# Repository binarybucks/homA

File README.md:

# HomA   

HomA is a free and open source framework for building smart homes and connecting them to the internet of things. 
It is designed to provide an entry into the world of home automation while also remaining highly extensible and adaptable for advanced users. 

To facilitate the development of own hardware and software extensions, HomA relies on completely open technologies and standards that are available on many platforms. Hence, it uses the lightweight and open [MQTT protocol](http://mqtt.org/faq) for both data storage and command transmission. 

### Getting started
Getting started with HomA is quite easy and requries just some basic Linux and commandline knowledge. For detailed installation instructions, please refer to the [Installation page](https://github.com/binarybucks/homA/wiki/Installation) on the Wiki.

### Components 
A list of offical components is available in the [wiki](https://github.com/binarybucks/homA/wiki/Components). 

### Contribute
Fork the repository on GitHub, add your own improvements, push it to a branch in your fork and send us a pull request. An overview of open tasks is available on the [Waffle.io](http://waffle.io/binarybucks/homA) dashboard.
You can also file bugs or feature requests in our [issue tracker](https://github.com/binarybucks/homA/issues) or say hi in our [Google+ Community](https://plus.google.com/u/0/communities/111676474572375715081).

### License
If not stated otherwise explicitly, any code in this repository is licensed under the EPL license.

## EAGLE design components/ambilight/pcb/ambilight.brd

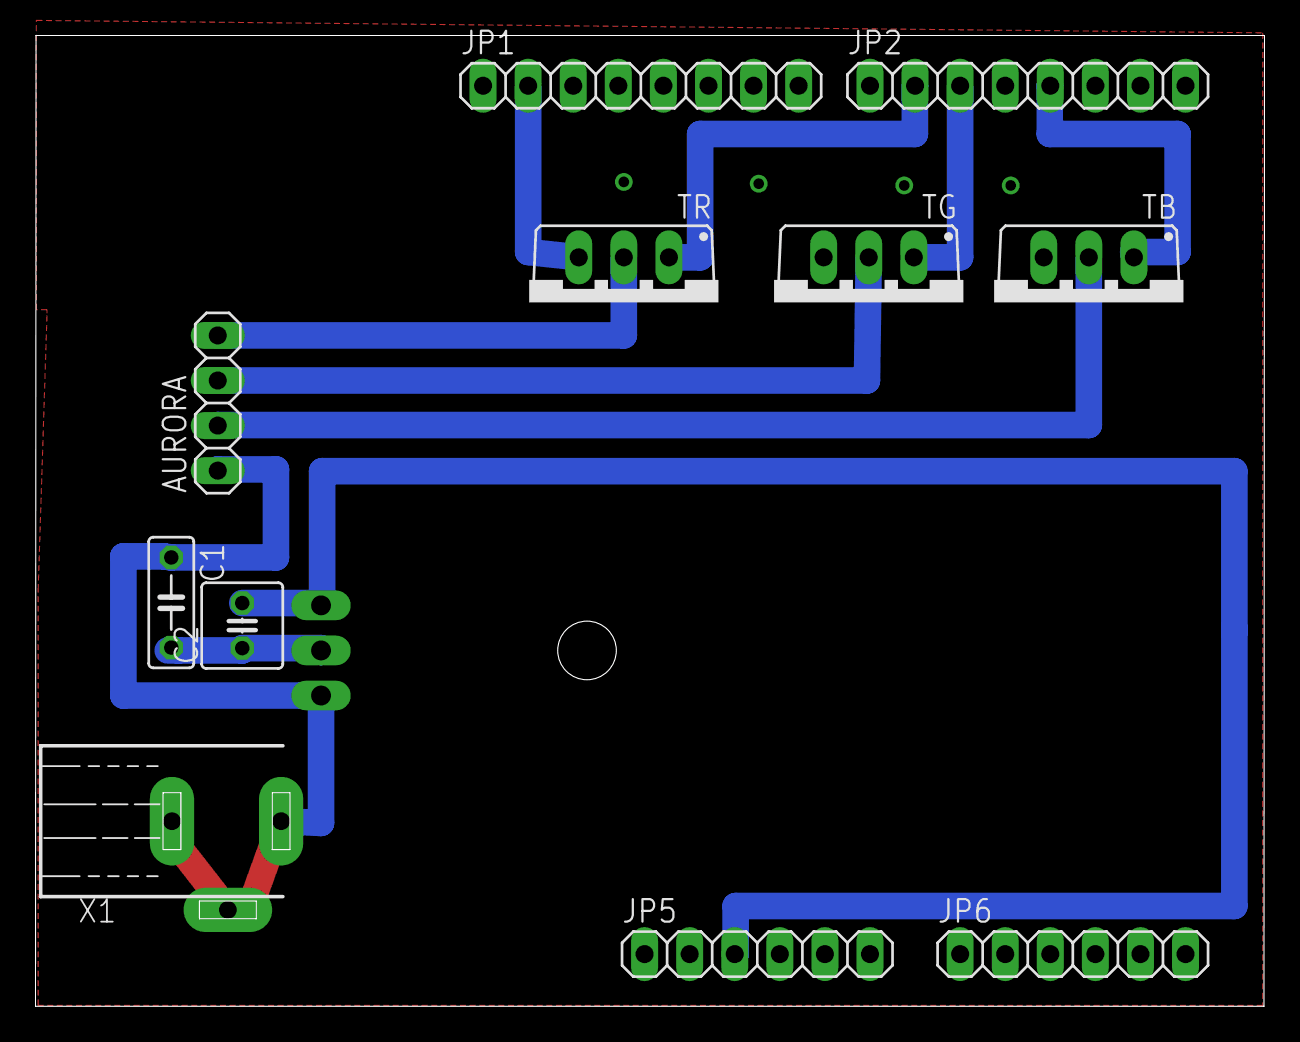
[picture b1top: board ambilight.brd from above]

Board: 2 copper layers, 69.2 x 54.7 mm, 12 parts (1 on the bottom side), 9 nets.

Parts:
AURORA: 1X04
C1: 330n; C050-025X075
C2: 100n; C025-050X050
IC1: 7805T; TO220H
JP1, JP2: 1X08
JP5, JP6: 1X06
TB: foo; TO220BV
TG: foo; TO220BV
TR: foo; TO220BV
X1: 733980-62

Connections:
GND: C1.2, C2.1, IC1.2, JP1.2, TB.S, TG.S, TR.S, X1.2, X1.3
unnamed: C2.2, IC1.3, JP5.3
unnamed: AURORA.1, C1.1, IC1.1, X1.1
unnamed: JP2.5, TB.G
unnamed: JP2.3, TG.G
unnamed: JP2.2, TR.G
unnamed: AURORA.4, TR.D
unnamed: AURORA.3, TG.D
unnamed: AURORA.2, TB.D

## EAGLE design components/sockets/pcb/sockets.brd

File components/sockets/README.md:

# HomA - Sockets
This component allows the control of generic 433Mhz wireless power sockets. 
If you have access to etching equipment, a schematic for a custom Arduino shield is included in the ```pcb``` directory. 

### Basic Requirements
* Arduino Uno or compatible
* Ethernet Shield (Anything with a W5100 Ethernet Chip)
* 433Mhz transmitter that is compatible with the [RC-Switch](https://code.google.com/p/rc-switch/) library. 

### Arduino Shield requirements
* Etching equipment
* 7805 Linear regulator
* SMA Jack
* 100nF Capacitor
* 330nF Capacitor
* Power Jack

### Installation
* Adapt the Arduino Sketch to your needs and flash it to your Arduino. 
* Adapt the MAC adress to something unique in your network
* Use a different CLIENTID if you are running more than one instance.

### Usage
To add a new typeA (10 Dip) wireless power socket
```
$ publish.js [--brokerHost 127.0.0.1] [--brokerPort 1883] --topic "/sys/CLIENTID/11011-01000" --payload "typeA"
```
Where 11011 is the position of the physical socket's group DIP switches, 01000 is the position of the socket's device DIP switches.

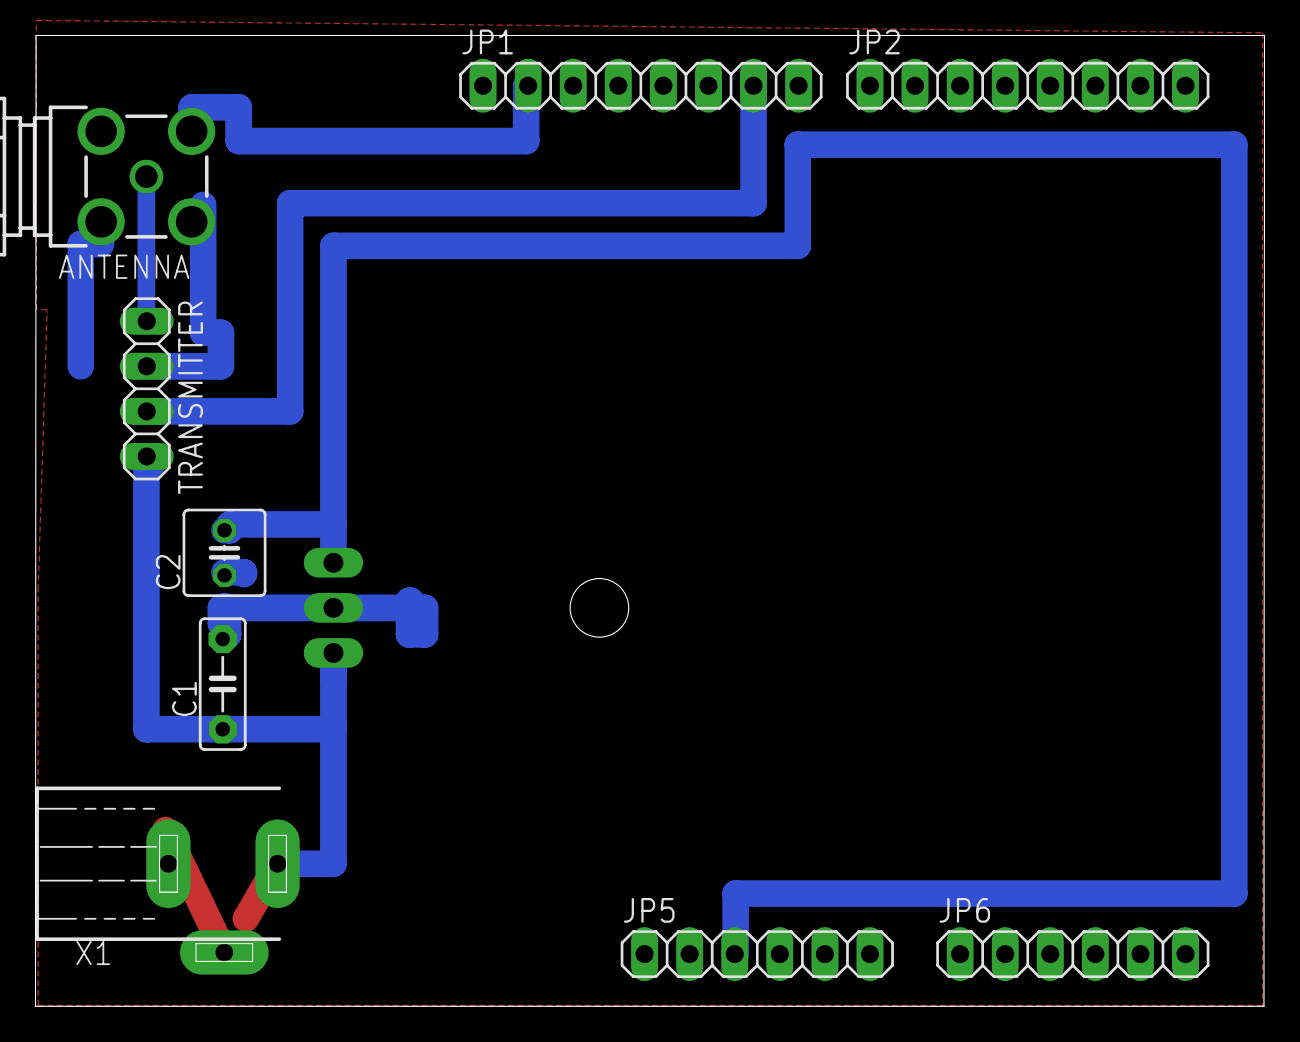
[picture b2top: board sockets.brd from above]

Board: 2 copper layers, 69.2 x 54.7 mm, 10 parts (1 on the bottom side), 5 nets.

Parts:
ANTENNA: BU-SMA-G
C1: 330n; C5B2.5
C2: 100n; C025-050X050
IC1: 7805T; TO220H
JP1, JP2: 1X08
JP5, JP6: 1X06
TRANSMITTER: 1X04
X1: 733980-62

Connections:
GND: ANTENNA.2, ANTENNA.3, ANTENNA.4, ANTENNA.5, C1.2, C2.1, IC1.2, JP1.2, TRANSMITTER.2, X1.2, X1.3
unnamed: C2.2, IC1.3, JP5.3
unnamed: C1.1, IC1.1, TRANSMITTER.4, X1.1
unnamed: JP1.7, TRANSMITTER.3
unnamed: ANTENNA.1, TRANSMITTER.1

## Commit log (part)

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2012-12-04 Added proguard settings, moving paho to bundled jar file
2012-12-04 Fixed preferences, Code Cleanup, Improved bootstrapAndConnect
2012-12-04 fixed issue #26
2012-12-04 Fixed rooms not clearing on server change
2012-12-13 Added rudimentary reconnect function to webinterface. Timeout is still quite high
2012-12-30 Added 433mhz sketch that allows for dynamic device configurations
2013-01-05 Arduino now reconnecting to broker automatically
2013-01-07 added garbage collector
2013-01-10 Refactored calendar quite a bit
2013-01-13 Fixed issue #33, #28, #11 (Not yet for android)
2013-01-13 Fixed issue #30, Provided a slightly smaller custom version of the Arduino Ethernet library that also allows to set a custom hostname
2013-01-20 Reorganized project structure
2013-01-23 Added new android project with swipe interface
2013-01-26 Got FragmentStateAdapter mostly working
2013-01-27 Moved strings to strings.xml files, fixed some null pointer exceptions
2013-01-27 Fixed nullpointer on orientation changes
2013-01-27 Added missing height attribute to device dialog
2013-01-28 Fixed wrong statis notification
2013-01-30 Derp
2013-02-05 Replaced dialog listview with custom view handling
2013-02-06 Added query method to calendar
2013-02-08 Added mqtt-http-bridge as submodule
2013-02-08 Merge
2013-02-08 lowered android app api version
2013-02-08 added node_modules to .gitignore file
2013-02-10 Refactored MainActivity, improved connection checking after network change
2013-02-10 Fixed controlView type derp
2013-02-10 Added correct notification icons, removed timestamp in notification
2013-02-10 Replaced orange list selection with blue list selection
2013-02-10 Fixed server adress input for now
2013-02-10 Cleaned up calendar
2013-02-10 Fixed publishing fail when payload was not a string
2013-02-11 Fixed issue #45
2013-02-12 Added not-connected placeholder image to Android MainActivity
2013-02-12 cleaned up server preference summary code
2013-02-13 added NfcActivity to Android app
2013-02-13 Catching empty events in calendar
2013-02-14 Added nfc capability
2013-02-17 Added NFC writing interface
2013-02-18 Fixed fail when NFC tag is not NDEF formated
2013-02-19 Added rule engine prototype
2013-02-19 Moved automation components to own folder
2013-02-19 Removed gc
2013-02-19 Ported cleaner tool to node.js
2013-02-19 Added some rule prototypes
2013-02-20 Fixed rotation change in NFCWriteActivity
2013-02-20 Now canceling sending of deferred mqtt message after NFC scan after 10 seconds
2013-02-21 Fixed typo in rules.js
2013-02-21 Now only updating clock when receiving new message
2013-02-21 Implemented issue #51
2013-02-21 Decreased mqttjs keepalive time
2013-02-21 Added home rule
2013-02-21 now using propper pings
2013-02-21 decreased ping freaquency
2013-02-22 Removed crappy try-catch
2013-02-23 Migrated all node.js applications to homa-mqttjs package
2013-02-23 Fixed publishing of empty strings
2013-02-23 Hopefully fixed rule loop problem by forgetting knowledge that triggered a rule so the rule does not match again if its publish is received
2013-02-25 Fixed issue #47
2013-02-25 Added some helper functions to node library
2013-02-25 Fixed derp
2013-02-25 Switched all node files to use npmlog
2013-02-25 Fixed wrong schedule of end events
2013-02-26 Set max value of range slider to 255
2013-02-26 Replaced srcElement by target
2013-02-26 Fixed some rules
2013-02-27 Could have fixed issue #55
2013-02-27 added solar readme
2013-03-04 Added makefile for easy updates of node modules
2013-03-04 Fixed make npm_update to work on linux
2013-03-05 Streamlined MqttService, Hopefully fixed issue #58, #59
2013-03-05 Changed mqttjs source back to official registry which now also contains version 0.2.1
2013-03-06 catched some issues that resulted from MQTT.js's API streamlining / breaking
2013-03-07 fixed connected bind
2013-03-07 fixed message bind
2013-03-07 Adde webinterface readme
2013-03-07 removed websocket-server submodule
2013-03-07 some cleanup and license foo
2013-03-07 Added EPL for the android App
2013-03-07 Implemented issue #64
2013-03-08 maybe dismissing dialog on disconnect
2013-03-08 fixed issue #67
2013-03-08 fixed issue #68, #69
2013-03-08 Worked on issue #54
2013-03-10 Added logger
2013-03-12 Updated homa node module to account for changes in mqtt module
2013-03-18 fixed compile errors
2013-03-19 Refactored fragment handling of MainActivity to fix issue #73 and everything NPE related in the activity
2013-03-21 updated to backbone.js 1.0
2013-03-22 Added Ambilight Arduino sketch
2013-03-25 Implementing issue #76
2013-03-26 mqtt disconnect onbeforeunload
2013-03-26 Fixes issue #78
2013-03-26 Disabled debug output
2013-03-27 Maybe fixes issue #79
2013-03-27 Fixes issue #80
2013-03-28 don't sanitize text in webinterface
2013-04-04 Added Socket PCB, fixed ambilight sketch a bit
2013-04-07 modified rules
2013-04-08 Required new version of mqtt node module
2013-04-08 updated homa mqtt module version
2013-04-08 Fixed ruleset to remove not working rule
2013-04-08 disabled debug
2013-04-10 Handling calendar event parse fails more gracefully
2013-04-16 Moved solar lat/long to /sys topics
2013-04-16 Added environment settings
2013-04-16 Added solar systemd service
2013-04-16 Added systemd services
2013-04-16 Added systemd service enable howto
2013-04-16 Included systemd in readmes
2013-04-16 Fixed merge conflict
2013-04-16 Commented calendar code
2013-04-16 Reduced node update depths
2013-04-23 Hopefully fixed wrong scheduling of calendar events
2013-04-29 Removed mosquitto.service (now contained in Arch mosquitto package), Added Bugsnag issue tracker to Android app
2013-04-30 Added systemd template, migrated rules to new systemd template
2013-04-30 migrated calendar component to new systemd template
2013-05-04 Worked on issue #88
2013-05-18 Added restart on-failure to systemd service file to reconnect after the connection to the broker has been lost
2013-05-18 Added additional ops to systemd service file
2013-05-18 Fixed make npm_update
2013-05-20 Worked on pcbs
2013-05-24 Implemented masonry card layout
2013-05-24 Updated WSS submodule
2013-05-25 Migrated code to use paho library
2013-05-29 Updated websocket-server
2013-05-30 Added masonry
2013-05-30 Fixed reconnect method
2013-05-30 Updated readmes with consistent definitions, Added CSM smartmeter component
2013-05-30 Got rid of ToplevelView class in webinterface, Now dynamically managing 'All' view
2013-05-30 Fixed issue #94, #5
2013-05-30 Fixed issue #87, #91
2013-05-31 Added architecture overview
2013-06-01 Interface work
2013-06-03 Fixed wrong systemId
2013-06-03 More paho tweaks
2013-06-03 Added demo component to for issue #100, Fixed readmes of other components that still included systemd-enable with template file
2013-06-03 Added wss binaries instead of fragile submodule
2013-06-03 Added wss readme
2013-06-03 updated to latest pahojs version
2013-06-06 fixed issue #104
2013-06-06 added version number display in android preferences
2013-06-06 Worked on issue #105
2013-06-07 Fixed PlaceholderView callback
2013-06-07 Fixed issue ä97
2013-06-08 Updated websocket server for arm. It is now the MQTT-aware version that should work with every Javascript MQTT client library
2013-06-09 Added Play Store promo images
2013-06-09 Fixed typo
2013-06-16 Added weather component, Added control/meta/ordering to sort a device's controls
2013-06-16 Fixed wrong websocket server release
2013-06-16 Fixed csm unit
2013-06-19 Added lastChange attribute to rules Message object, temporary fix for webinterface disconnect issues, matched wss default port to 18883 (issue #111, /cc issue #107)
2013-06-19 Updated default websocketPort
2013-06-19 Added back navigation when saving preferences for issue #108
2013-06-19 Removed link outline when clicked
2013-06-20 Added workaround for issue #113
2013-06-23 Cleaned up strings, fixed issue #115, validating server preference input and conditionally enabling/disabling connect and disconnect buttons
2013-06-23 Added German translation
2013-06-29 Some cleanup
2013-06-30 Disabled outlines and text selection for controls
2013-07-02 updated Raspberry Pi websocket server binary to the latest version (#117)
2013-07-03 Added new version of WSS_osx for issue #117
2013-07-10 Added webinterface image control for issue #116
2013-07-11 started to implement quick-publish infrastructure
2013-07-11 Exposing extra params of mqtt.createClient in mqttHelper for issue #119
2013-07-12 Added combined edit/add dialog fragment
2013-07-12 exposing further parameters for issue #119
2013-07-13 Increased node module version number
2013-07-16 add waffle.io badge
2013-07-29 Closes issue #122
2013-07-29 websocket server binary for the raspberry pi is the same version (0.5) as the others now. The last update fixed issues with long mqtt messages.
2013-10-20 added qp things
2013-11-03 Closes #110, #109, #118
2013-11-03 closes #127
2014-01-04 Fixed drawer issues, Fixed TLS custom cert options
2014-03-13 my first ever pull request commit: homA solar readme
2014-03-13 minor change: homA solar readme
2015-03-15 README Fix link to the installation page
    fixes #133
2015-04-20 added min attribute to slider
2015-04-20 Set correct unchecked status for checkbox slider
2015-04-23 Fix checkbox styling so it can be switched by pressing anywhere on the button whilst still having the correct styling in firefox. Fixes part of binarybucks/homA#85
2015-08-28 made control ID's unique (derived from topic string), added controlName for naming them. fixed #139
2016-03-05 new slider css (the old one did not work in chrome any more)
2016-03-05 range css now even works in IE11 (kind of ...) and edge
2017-02-23 - fixed a bug in the order of the weather controls - openweathermap.org is free, but you now need to register to get an API key (appid) added a new sys setting "key" for that
2017-03-03 added device meta values
2017-03-03 fixed typing
2017-03-03 - added Python byte code files to .gitignore - added private mqtt_config.py to .gitignore - fixed energy script to be path independent
2017-03-09 rcplugs initial revision
2017-04-06 rcplugs: modified to be complient with issue #144 and sockets component energy: added meta/unit topic and removed unit from payload of actual value
2017-04-07 added commentadded comment
2017-04-07 corrected comment
2017-04-07 simplyfied get_topic code, minor changes
2017-06-13 added new component "windsensor"
2017-07-09 fixed counting fast pulses, added daylight saving time adjustment, pushed to version 14
2017-07-09 ignore Eagle backup files
2017-07-09 changed cross compiler link, added schematics link
2017-07-09 removed lib mbedtls and SSL code from mqtt (by not defining MQTT_SSL_ENABLE), saves about 100k code
2017-10-30 fixed some Makefile issues, added reset reason mqtt message, changed qos of some mqtt messages, recompiled with new SDK 2.1.0 (deb1901) fixing the KRACK vulnerability
2017-11-01 optimized startup procedure, reduced traffic by sending only changed speed values
2017-11-03 added universal min/max saver component
2017-12-09 Optimised code to compile with g++ too (changed "strings" to char*, added missing casts, added missing includes). Needs some changes in esp sdk as well. I will write an issue there ...
2017-12-24 added command line switch to remove the persistant messages, changes for new "on room" feature
2018-01-11 added wiringESP submodule
2018-01-11 added rc-switch submodule
2018-01-11 Initial revision
2018-01-11 fix bug in c_types.h include, not defining BOOL, TRUE, FALSE for c++
2018-02-05 v27: added output of some status information (.Info) to mqtt, fixed schematics issue with rx/tx
2018-02-25 added .settings to -gitignore
2018-03-12 changes device name of power D and E, added meta/room and meta/name to show all the plugs in one room
2018-03-18 SDKs gen_appbin.py is not set executable, added python command before script
2018-03-18 renamed rcswitch to rcplugs
2018-03-18 updated some comments, changed 0 to FALSE for better readabilaty
2018-03-18 renamed SPEED_TASK to MAIN_TASK
2018-03-24 moved component garage to homA-components
2018-03-24 moved component rcplugs-rpi to homA-components
2018-03-24 moved component windsensor to homA-components
